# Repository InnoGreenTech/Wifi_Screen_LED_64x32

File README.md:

Wifi Matrix screen led 32x64  connected
====================

Description:
------------

This is a LED SCREEN 32x64 1/8 scan.

There are web pages to configure and to sent new messages. 

[*You can also follow this project here*](http://innogreentech.fr) 

[*A complete description to make electronic boards*](http://innogreentech.fr/fr/objets-connectes/11-interfaces/66-fabriquer-un-afficheur-led-32x64-connecte)

[*Also a video that show the building from a to z*](https://www.youtube.com/watch?v=SuA-KLQndhk&t=924s)

!

Contributing:
-------------

Fork it
Create your feature branch (git checkout -b my-new-feature)
Commit your changes (git commit -am 'Add some feature')
Push to the branch (git push origin my-new-feature)
Create new Pull Request

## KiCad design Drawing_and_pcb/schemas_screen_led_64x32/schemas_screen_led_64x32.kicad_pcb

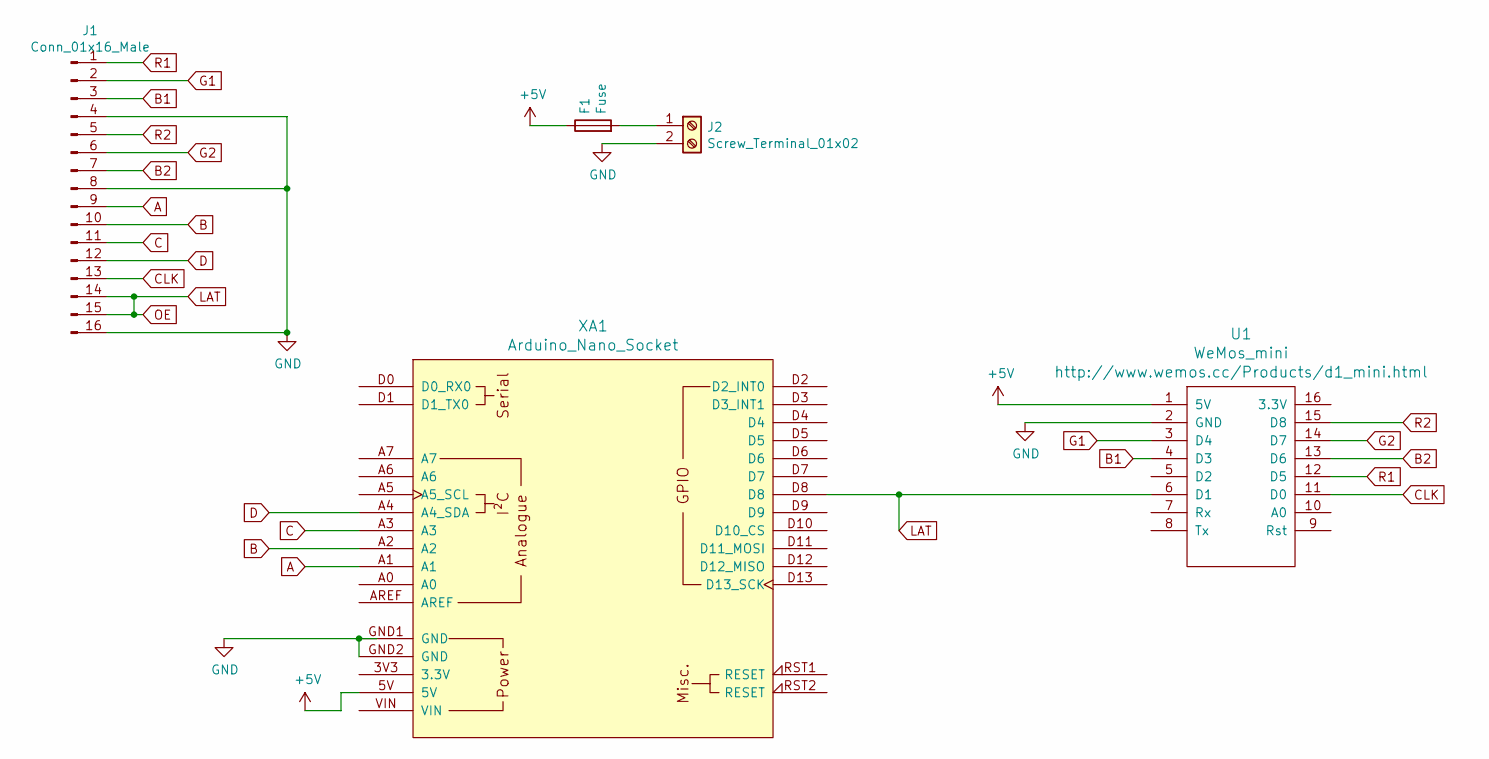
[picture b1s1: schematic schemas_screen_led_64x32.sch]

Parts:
F1: Fuse; R_Axial_DIN0614_L14.3mm_D5.7mm_P15.24mm_Horizontal
J1: Conn_01x16_Male; IDC-Header_2x08_P2.54mm_Vertical
J2: Screw_Terminal_01x02; TerminalBlock_4Ucon_1x02_P3.50mm_Horizontal
U1: WeMos_mini; D1_mini_board
XA1: Arduino_Nano_Socket

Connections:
+5V: F1.1, U1.1 (5V), XA1.5V
A: J1.9, XA1.A1
B: J1.10, XA1.A2
B1: J1.3, U1.4 (D3)
B2: J1.7, U1.13 (D6)
C: J1.11, XA1.A3
CLK: J1.13, U1.11 (D0)
D: J1.12, XA1.A4 (A4_SDA)
G1: J1.2, U1.3 (D4)
G2: J1.6, U1.14 (D7)
GND: J1.4, J1.8, J1.16, J2.2, U1.2 (GND), XA1.GND1 (GND), XA1.GND2 (GND)
LAT: J1.14, J1.15, U1.6 (D1), XA1.D8
unnamed: F1.2, J2.1
R1: J1.1, U1.12 (D5)
R2: J1.5, U1.15 (D8)

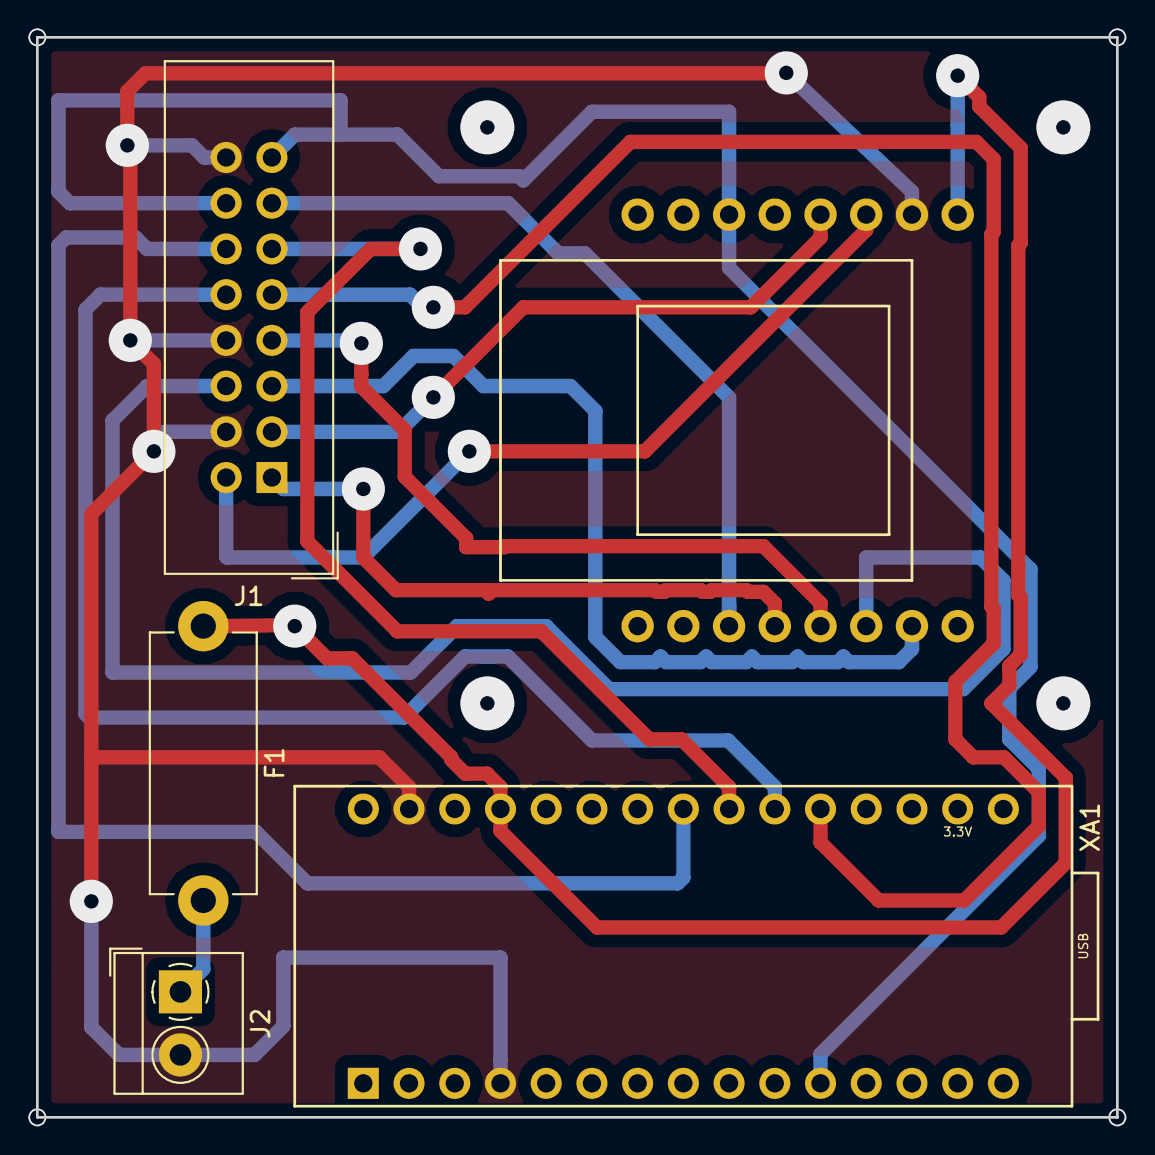
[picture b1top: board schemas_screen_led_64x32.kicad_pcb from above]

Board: 2 copper layers, 60.0 x 60.0 mm, 5 parts (1 on the bottom side), 15 nets.

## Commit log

2020-03-14 add read me file
2020-03-24 update read me file
2020-04-04 add possibiliy to display date an time in the first message. For this use command or , just one on the both first lines and both on the fird line.
